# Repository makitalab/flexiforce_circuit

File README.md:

# flexiforce_circuit
for using flexiforce, a mechanical pressure sensor

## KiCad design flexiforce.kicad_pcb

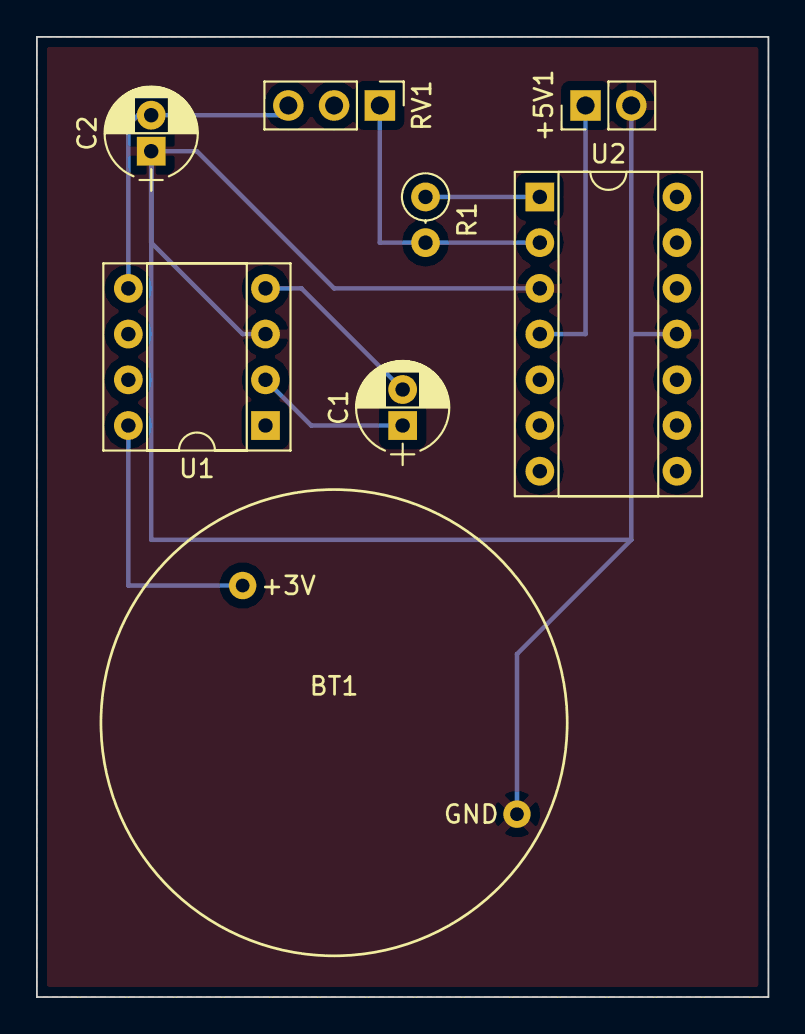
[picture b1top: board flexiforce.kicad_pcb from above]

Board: 2 copper layers, 40.6 x 53.3 mm, 8 parts (0 on the bottom side), 8 nets.

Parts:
+5V1: Power; Pin_Header_Straight_1x02_Pitch2.54mm
BT1: 3V; CR2032_flat
C1, C2: 10uF; CP_Radial_D5.0mm_P2.00mm
R1: RVAR; R_Axial_DIN0207_L6.3mm_D2.5mm_P2.54mm_Vertical
RV1: POT; Pin_Header_Straight_1x03_Pitch2.54mm
U1: ICL7660; DIP-8_W7.62mm_Socket
U2: MCP6004; DIP-14_W7.62mm_Socket

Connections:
+5V: +5V1.1, U2.4
GND: +5V1.2, BT1.2, C2.1, U1.3, U2.3, U2.11
unnamed: BT1.1, U1.8
unnamed: C1.1, U1.2
unnamed: C1.2, U1.4
unnamed: C2.2, RV1.3, U1.5
unnamed: R1.1, U2.1
unnamed: R1.2, RV1.1, U2.2

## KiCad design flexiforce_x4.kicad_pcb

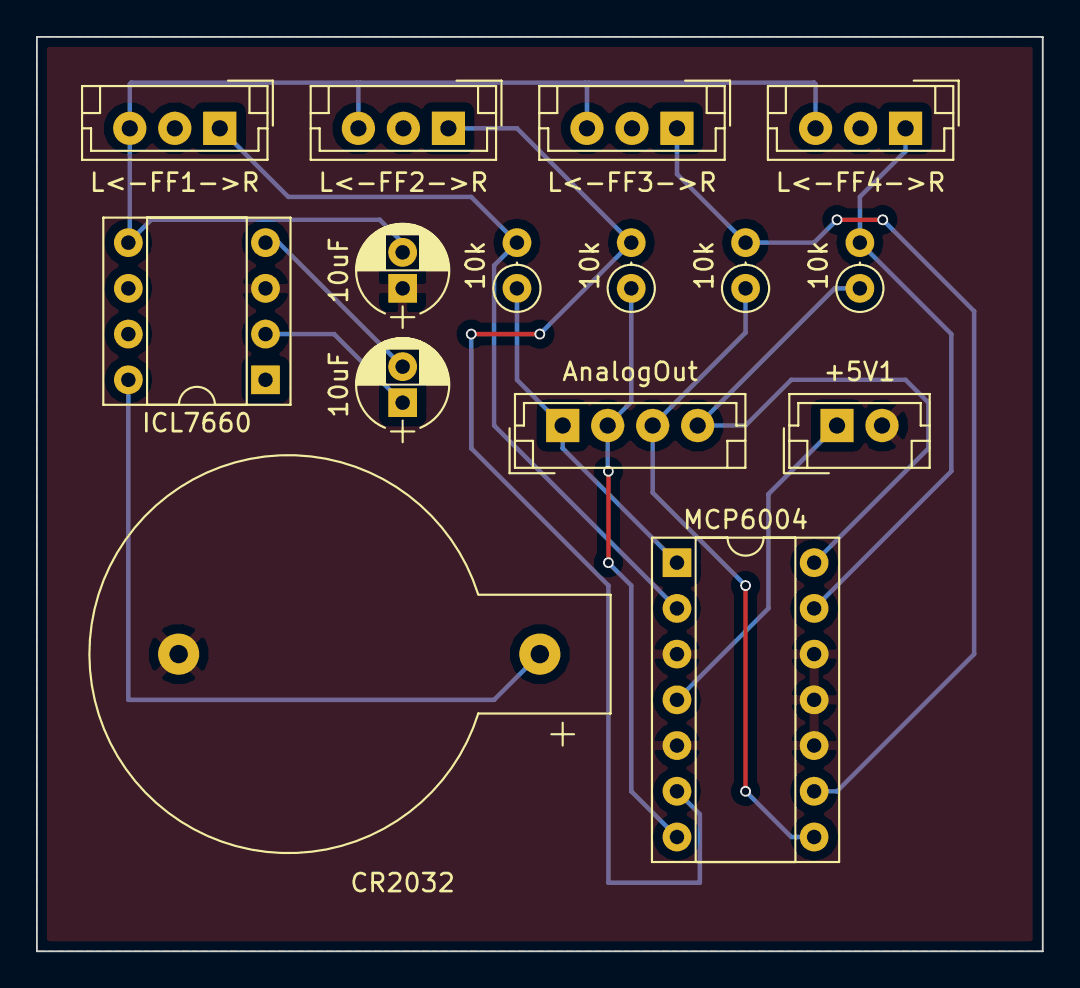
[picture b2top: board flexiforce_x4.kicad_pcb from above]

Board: 2 copper layers, 55.9 x 50.8 mm, 15 parts (0 on the bottom side), 14 nets.

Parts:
10k, 10k#2, 10k#3, 10k#4: 10k; R_Axial_DIN0207_L6.3mm_D2.5mm_P2.54mm_Vertical
10uF, 10uF#2: 10uF; CP_Radial_D5.0mm_P2.00mm
+5V1: Power; JST_EH_B02B-EH-A_02x2.50mm_Straight
AnalogOut: CONN_01X04; JST_EH_B04B-EH-A_04x2.50mm_Straight
CR2032: 3V; CR2032H
ICL7660: ICL7660; DIP-8_W7.62mm_Socket
L<-FF1->R, L<-FF2->R, L<-FF3->R, L<-FF4->R: POT; JST_EH_B03B-EH-A_03x2.50mm_Straight
MCP6004: MCP6004; DIP-14_W7.62mm_Socket

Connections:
+5V: +5V1.1, MCP6004.4
GND: 10uF#2.1, +5V1.2, CR2032.2, ICL7660.3, MCP6004.3, MCP6004.5, MCP6004.10, MCP6004.11, MCP6004.12
unnamed: 10uF.1, ICL7660.2
unnamed: 10uF.2, ICL7660.4
unnamed: 10uF#2.2, ICL7660.5, L<-FF1->R.3, L<-FF2->R.3, L<-FF3->R.3, L<-FF4->R.3
unnamed: CR2032.1, ICL7660.8
unnamed: 10k.1, AnalogOut.1, MCP6004.1
unnamed: 10k#2.1, AnalogOut.2, MCP6004.7
unnamed: 10k#3.1, AnalogOut.3, MCP6004.8
unnamed: 10k#4.1, AnalogOut.4, MCP6004.14
unnamed: 10k.2, L<-FF1->R.1, MCP6004.2
unnamed: 10k#2.2, L<-FF2->R.1, MCP6004.6
unnamed: 10k#3.2, L<-FF3->R.1, MCP6004.9
unnamed: 10k#4.2, L<-FF4->R.1, MCP6004.13

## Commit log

2017-12-20 first commitment
